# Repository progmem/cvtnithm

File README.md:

# CVTnithm

CVTnithm is a cable adapter in PCB form. That's about it!

Thanks to [@48productions](https://github.com/48productions) who made a guide on how to make all the necessary wiring and made me realize:

* Digikey doesn't sell the crimpable version of the connector
* I'm not buying a single part from JST directly
* also i don't want to buy a specialty crimper for molex pins (_except i kinda had to for handling ac power lmao_)
* also i'm lazy, but not lazy enough to make a pcb

## I'm sorry I didn't have a creative name for this project

To build this, you will need the following components:

* For the serial connections:
  * (1) [JST B22B-XADSS-N](https://www.digikey.com/en/products/detail/jst-sales-america-inc/B22B-XADSS-N-LF-SN/1300311)
  * (3) 2x5 IDC box headers, such as [SBH11-PBPC-D05-ST-BK](https://www.digikey.com/en/products/detail/sullins-connector-solutions/SBH11-PBPC-D05-ST-BK/1990062)
* For the power connections:
  * (1) [Molex Mini-Fit Jr. 5556](https://www.digikey.com/en/products/detail/molex/0039310140/2405381)
  * (2) PC 4-pin power connectors, such as [TE MATE-N-LOK 350211-1](https://www.digikey.com/en/products/detail/te-connectivity-amp-connectors/350211-1/30127)
    * NOTE: This connector works, but it is a _royal pain_ to disconnect the cable once it's plugged in.
* A CVTnithm PCB. Two options are provided:
  * The `alls` folder contains the PCB files used for an ALLS, such as an ALLS UX.
  * The `nu-alls` folder contains the PCB files for a Nu1.1-ALLS conversion.

Connecting this board internally requires the following:

* (3) 2x5 IDC cables, such as [these on Amazon](https://www.amazon.com/dp/B07FZWWGY3). The cables should be a straight connection without any twists or other modification. 

Solder each of these connectors in their respective places; each connector has a unique footprint so it should be fairly obvious what connectors need to go where. Be mindful of orientation!

## So I soldered this, now what?

* On an ALLS, remove the serial brackets by undoing the two PCI bracket screws, unplugging them from the motherboard in the process.
* Locate a suitable set of power cables.
  * In an ALLS, locate the collection of unused power supply cables. Undo this bundle and find a cable containing two PC 4-pin power connectors and a floppy drive connector.
  * In a Nu1.1-ALLS conversion, this will vary wildly depending on the power supply used. You will need two PC 4-pin power connectors, from one or two cables.
* Note the `COM_` number on each of the serial ports on the motherboard. Plug one IDC cable into each of the serial ports. Plug the other end into the CVTnithm PCB into its respective `COM_` port.
* Plug in the two PC 4-pin power connectors.

## How do I mount the ALLS PCB?

Print the two 3MF files in the `alls` folder in the orientations provided. The bottom bracket requires support material, and it's recommended to disable support for bridges as a small tool (like a dental pick) will be needed to clean out some of the support material otherwise. If you cannot disable support for bridges (due to slicer or printer limitations), you may try printing with the part upside-down as this will allow you to more easily clean out the support material.

With the rear of the ALLS facing you (herein described as the "front"), install everything as follows:

* Insert the bottom bracket into the two empty PCI slots from the _front_. The flat side should be facing you, with the `U` shape upward.
* Slide the bottom bracket as far down as you can. The metal of the PCI bracket should slide into a notch in the print.
* Looking at the ALLS from the top, fit the CVTnithm PCB into the notch in the bottom bracket. The CVTnithm board will be installed _inside_ the ALLS, with the IDC connectors facing downward.
* Place the top bracket over the CVTnithm PCB so the flat side is facing you, with the screw hole towards you. Reinstall the two PCI screws, making sure the CVTnithm PCB is retained by the bracket.

## How do I mount the Nu1.1-ALLS PCB?

Install the CVTnithm PCB where the AMEX PCB was previously installed with four screws. Text should be upright with the serial and DC output connectors facing outward.

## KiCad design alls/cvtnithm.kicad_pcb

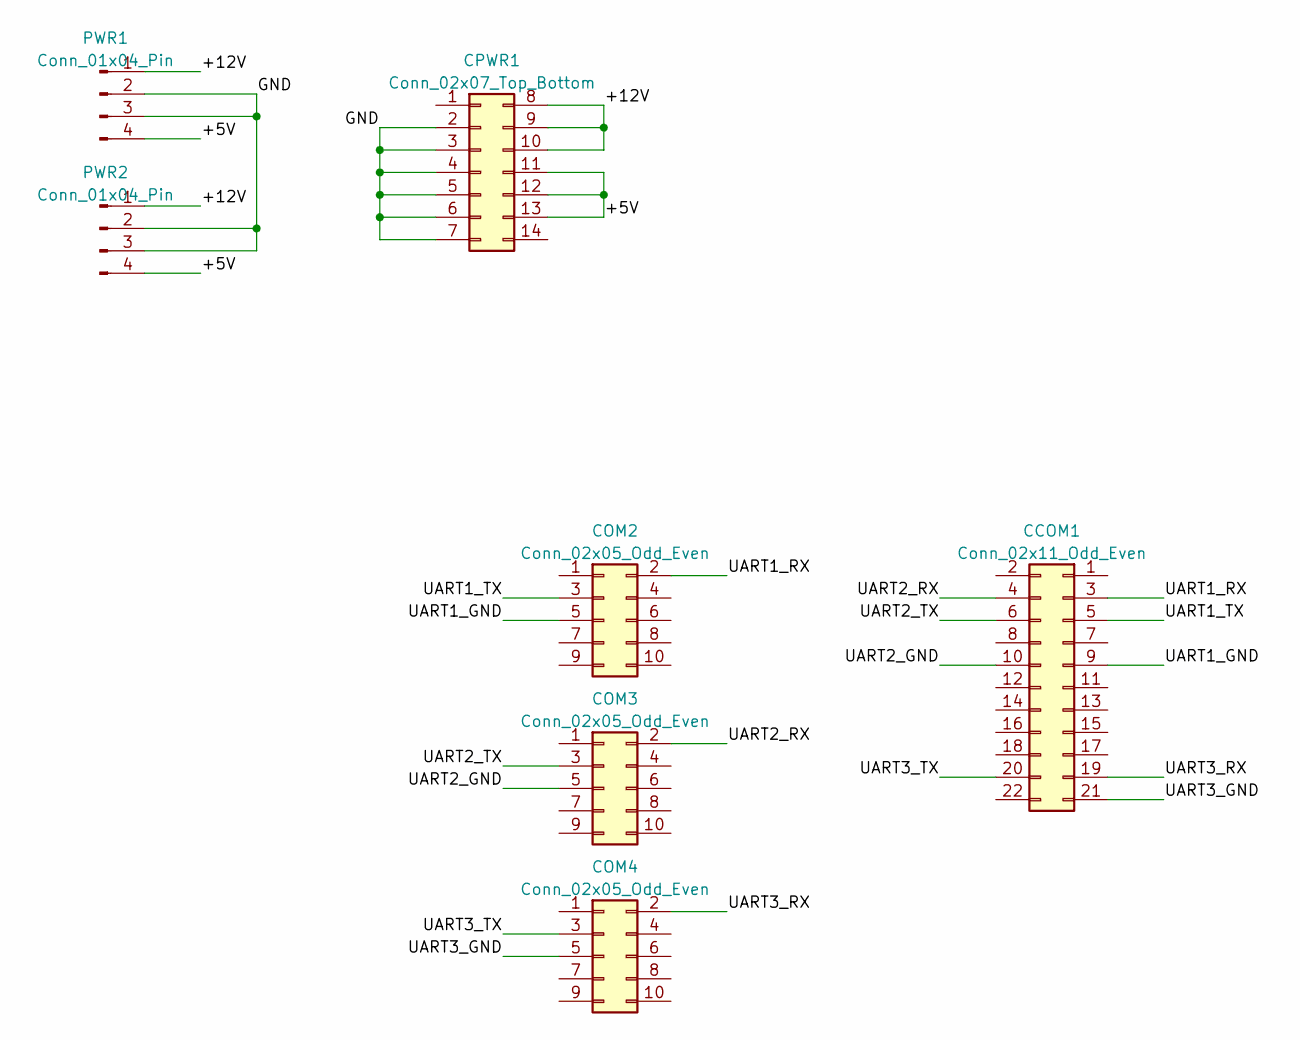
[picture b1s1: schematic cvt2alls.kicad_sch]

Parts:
CCOM1: Conn_02x11_Odd_Even; JST_XAD_B22B-XADSS-1_2x11_P2.50mm_Vertical
COM2, COM3, COM4: Conn_02x05_Odd_Even; IDC-Header_2x05_P2.54mm_Vertical
CPWR1: Conn_02x07_Top_Bottom; Molex_Mini-Fit_Jr_5566-14A_2x07_P4.20mm_Vertical
PWR1, PWR2: Conn_01x04_Pin; TE_MATE-N-LOK_350211-1_1x04_P5.08mm_Vertical

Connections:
/+5V: CPWR1.11, CPWR1.12, CPWR1.13, PWR1.4, PWR2.4
/+12V: CPWR1.8, CPWR1.9, CPWR1.10, PWR1.1, PWR2.1
/GND: CPWR1.2, CPWR1.3, CPWR1.4, CPWR1.5, CPWR1.6, CPWR1.7, PWR1.2, PWR1.3, PWR2.2, PWR2.3
/UART1_GND: CCOM1.9, COM2.5
/UART1_RX: CCOM1.3, COM2.2
/UART1_TX: CCOM1.5, COM2.3
/UART2_GND: CCOM1.10, COM3.5
/UART2_RX: CCOM1.4, COM3.2
/UART2_TX: CCOM1.6, COM3.3
/UART3_GND: CCOM1.21, COM4.5
/UART3_RX: CCOM1.19, COM4.2
/UART3_TX: CCOM1.20, COM4.3

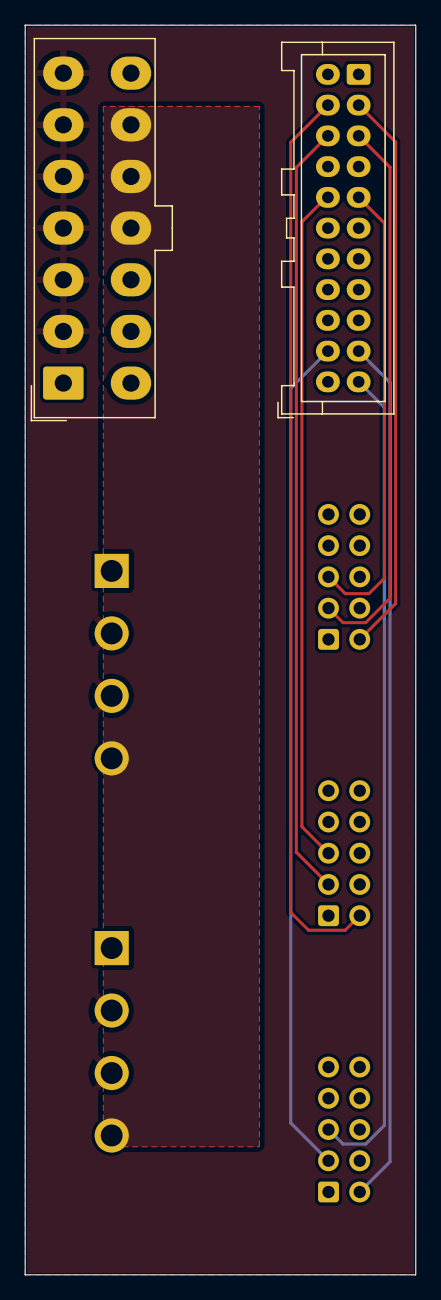
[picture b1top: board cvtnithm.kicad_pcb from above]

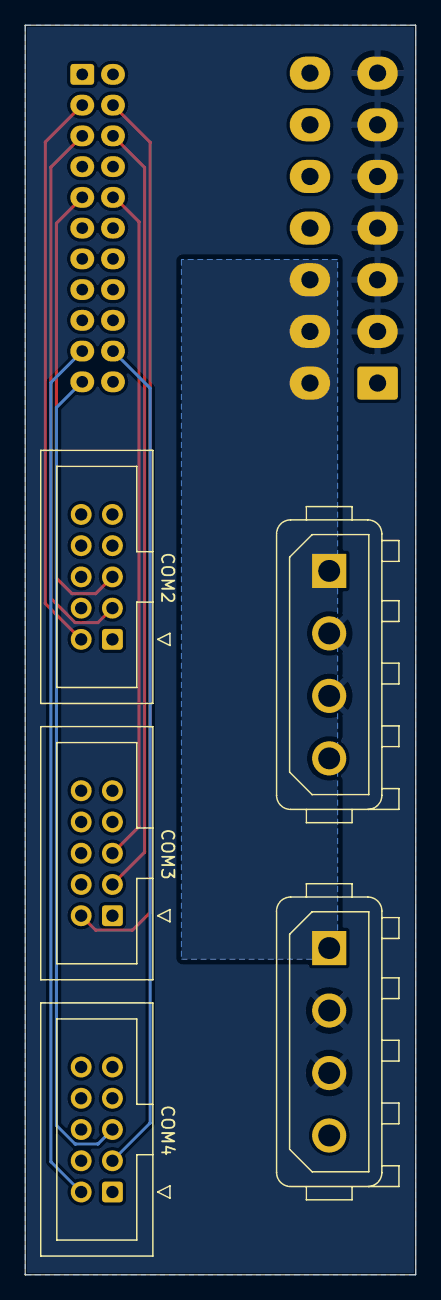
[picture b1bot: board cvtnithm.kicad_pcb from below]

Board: 2 copper layers, 31.8 x 101.6 mm, 7 parts (5 on the bottom side), 12 nets.

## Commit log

2024-01-08 Add 3D prints
2024-01-08 Add a README
2024-01-08 Add credits?
2024-01-08 Note the need for support material!
2024-01-08 Name change for clarity
2024-01-08 Rename files
2024-03-10 Update 3D printing recommendations, adjust parts for easier printability and slicing
2025-02-09 Add the Nu1.1-ALLS conversion PCB
